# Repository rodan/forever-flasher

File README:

'forever' blinker circuit - based on vk2zay's video [1]

most of the parts are 0805, including the led. power can come either from a 12mm coin cell Li (CR1220, CR1225) or a 1.5 battery.
in case the Li battery is used you should break the traces that go to the 2 pin external connector and use the now unconnected 2 holes to fasten the circuit to anything you want.

digikey part numbers:
    12mm battery holder:  3000KCT-ND
    BC847BPN:             568-1634-1-ND

[1]  http://www.youtube.com/watch?v=JenPZMHREfg

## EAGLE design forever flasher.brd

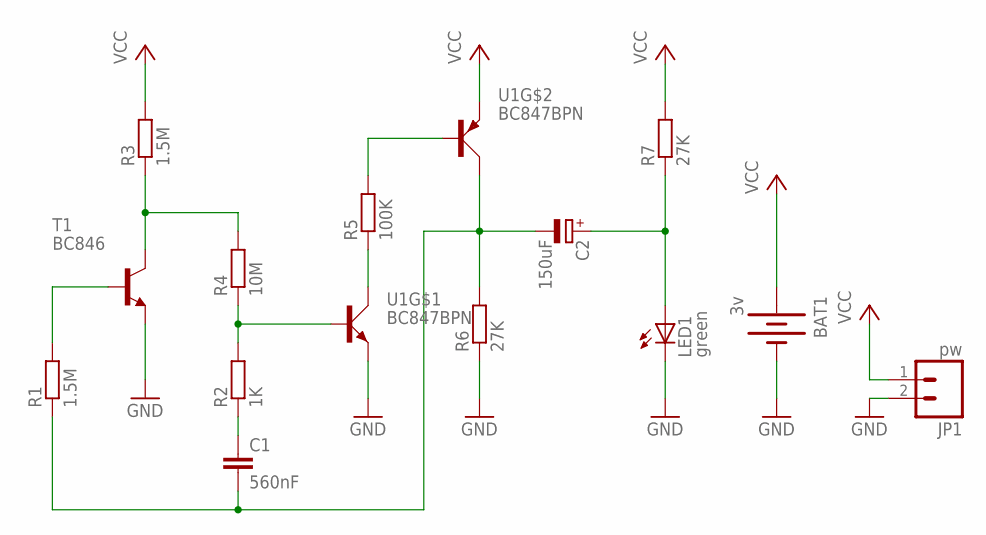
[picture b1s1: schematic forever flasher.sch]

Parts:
BAT1: 3v; BATTCON_12MM
C1: 560nF; C0805
C2: 150uF; CT7343
JP1: pw; 1X02
LED1: green; CHIPLED_0805
R1, R3: 1.5M; R0805
R2: 1K; R0805
R4: 10M; R0805
R5: 100K; R0805
R6, R7: 27K; R0805
T1: BC846; SOT23
U1: BC847BPN; SOT363_PHILIPS

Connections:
GND: BAT1.GND (-), JP1.2, LED1.C, R6.1, T1.2 (E), U1.1 (E)
unnamed: R1.2, T1.1 (B)
unnamed: R3.1, R4.2, T1.3 (C)
unnamed: C1.2, C2.-, R1.1, R6.2, U1.3 (C)
unnamed: C1.1, R2.1
unnamed: R2.2, R4.1, U1.2 (B)
unnamed: R5.2, U1.5 (B)
unnamed: R5.1, U1.6 (C)
unnamed: C2.+, LED1.A, R7.1
VCC: BAT1.PWR@1 (+), JP1.1, R3.2, R7.2, U1.4 (E)

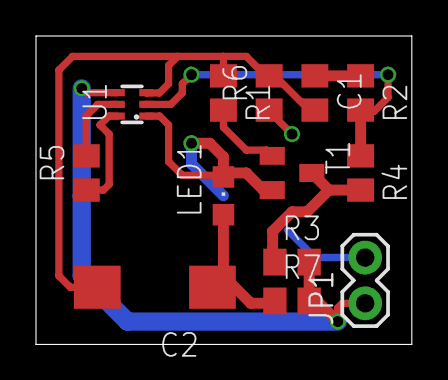
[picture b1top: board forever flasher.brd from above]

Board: 2 copper layers, 20.9 x 17.1 mm, 14 parts (1 on the bottom side), 10 nets.
